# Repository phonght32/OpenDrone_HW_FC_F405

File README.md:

# OpenDrone_FC_F405_HW

Version 3.0

### Overview

OpenDrone Project - Fly Controller hardware using STM32F405RG.

### Specifications

### Layout/Pin map

### Design

#### Schematic

#### PCB

F.Cu

B.Cu

#### 3D top

#### 3D bottom

#### Dimension

### Bill of materials (BOM)

[Download v1.0](Assets/BOM/BOM_OpenDrone_FC_F405_HW_v1.0.xlsx)

[Download v2.0](Assets/BOM/BOM_OpenDrone_FC_F405_HW_v2.0.xlsx)

[Download v3.0](Assets/BOM/BOM_OpenDrone_FC_F405_HW_v3.0.xlsx)

### Gerber

[Download v1.0](Assets/Gerber/Gerber_OpenDrone_FC_F405_HW_v1.0.zip)

[Download v2.0](Assets/Gerber/Gerber_OpenDrone_FC_F405_HW_v2.0.zip)

[Download v3.0](Assets/Gerber/Gerber_OpenDrone_FC_F405_HW_v3.0.zip)

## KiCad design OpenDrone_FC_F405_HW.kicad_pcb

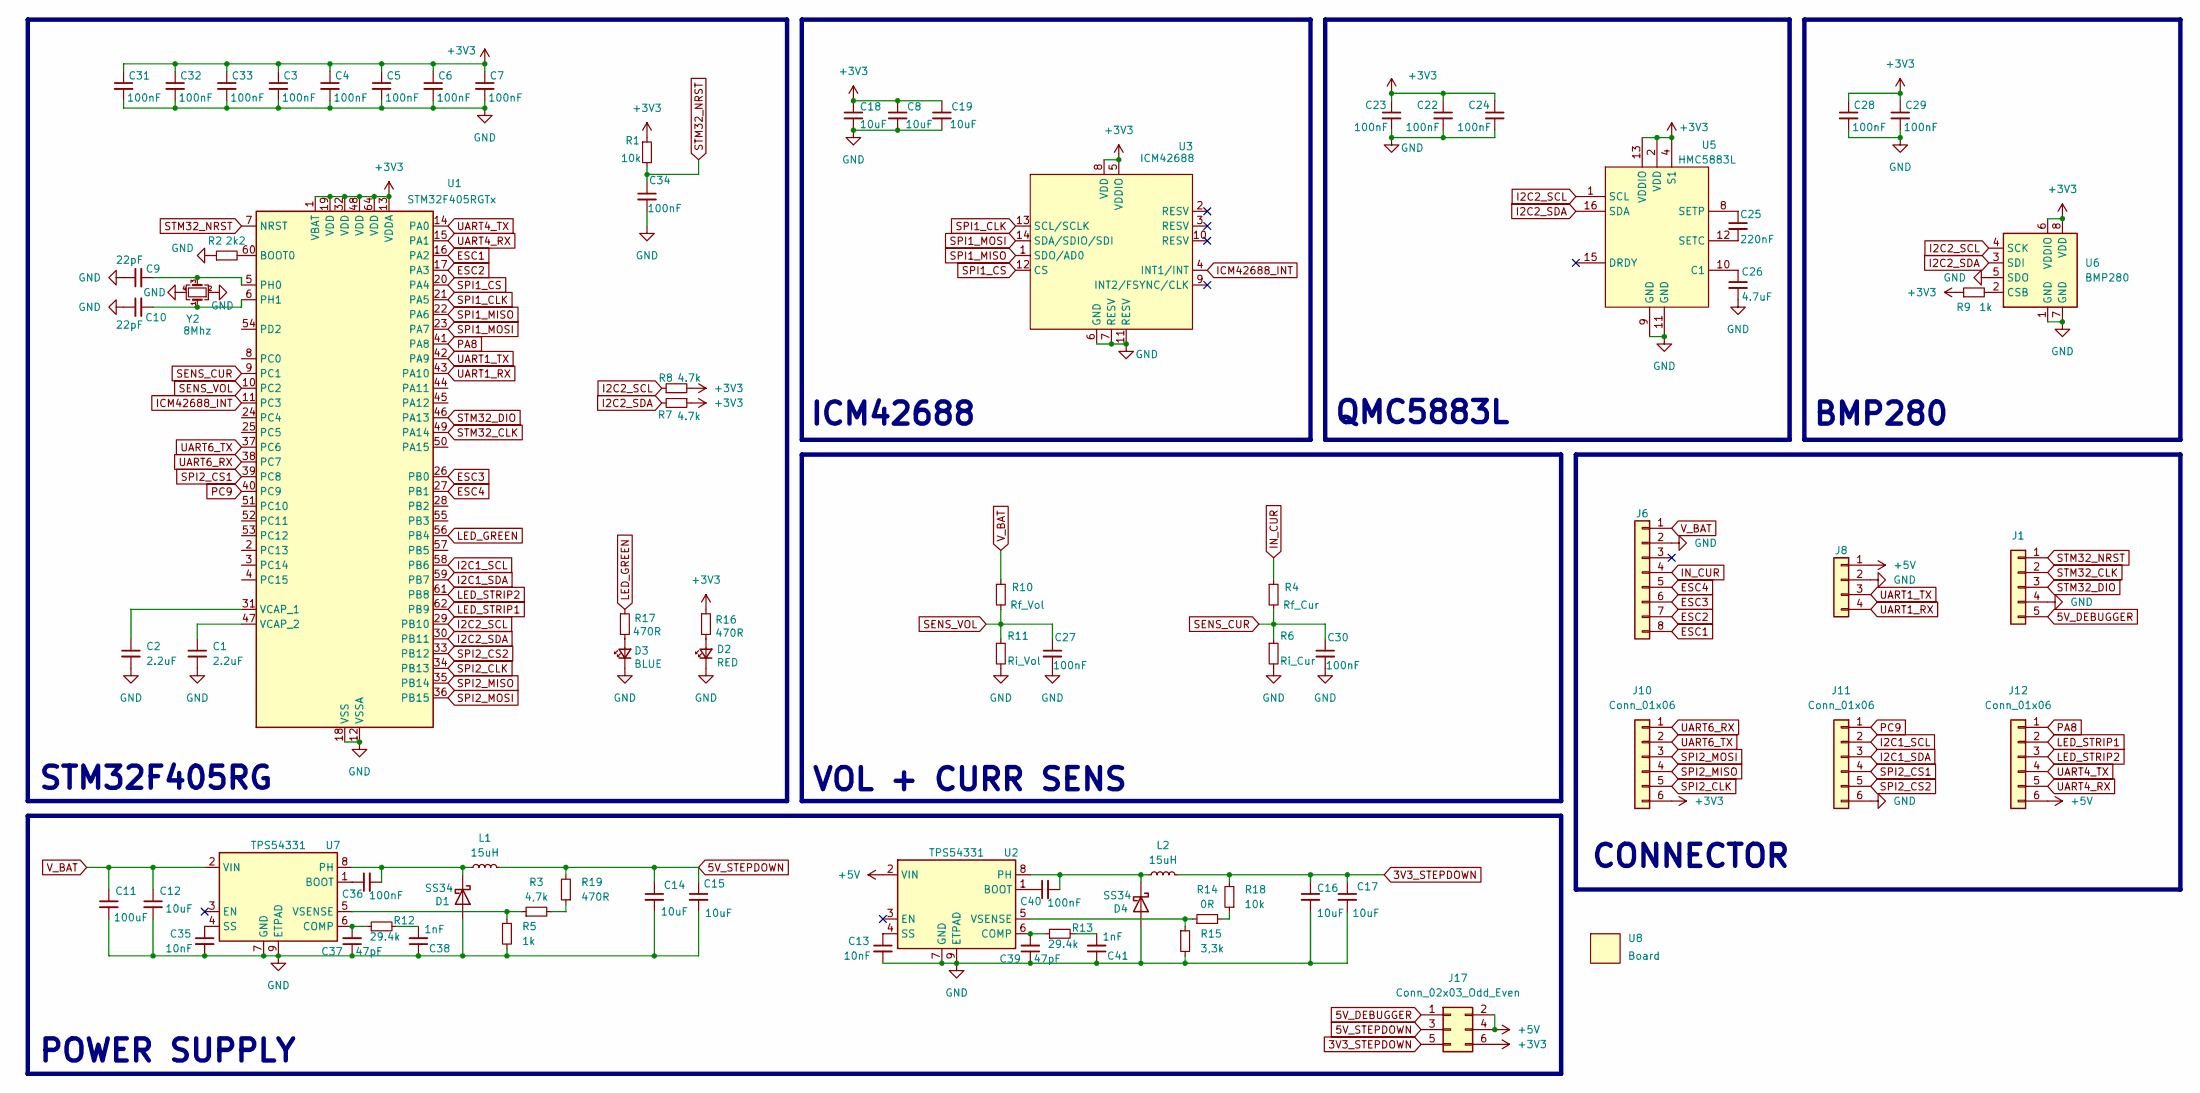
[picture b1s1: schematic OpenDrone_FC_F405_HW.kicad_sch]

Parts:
C1, C2: 2.2uF; C_0402_1005Metric
C3, C4, C5, C6, C7, C22, C23, C24, C27, C28, C29, C30, C31, C32, C33, C34, C36, C40: 100nF; C_0402_1005Metric
C8, C18, C19: 10uF; C_0402_1005Metric
C9, C10: 22pF; C_0402_1005Metric
C11: 100uF; C_1210_3225Metric
C12, C14, C15, C16, C17: 10uF; C_1210_3225Metric
C13, C35: 10nF; C_0402_1005Metric
C25: 220nF; C_0402_1005Metric
C26: 4.7uF; C_0402_1005Metric
C37, C39: 47pF; C_0402_1005Metric
C38, C41: 1nF; C_0402_1005Metric
D1, D4: SS34; D_SMA
D2: RED; LED_0402_1005Metric
D3: BLUE; LED_0402_1005Metric
J1: Conn_01x05; Connector_XH_1x05_P1.25mm_Horizontal
J6: Conn_01x08; Connector_XH_1x08_P1.25mm_Horizontal
J8: Conn_01x04; Connector_XH_1x04_P1.25mm_Horizontal
J10, J11, J12: Conn_01x06; Header_1x06_P2.00mm_Vertical
J17: Conn_02x03_Odd_Even; PinHeader_2x03_P2.00mm_Vertical
L1, L2: 15uH; Inductor_SMD_4D28
R1, R18: 10k; R_0402_1005Metric
R2: 2k2; R_0402_1005Metric
R3: 4,7k; R_0402_1005Metric
R4: Rf_Cur; R_0402_1005Metric
R5, R9: 1k; R_0402_1005Metric
R6: Ri_Cur; R_0402_1005Metric
R7, R8: 4.7k; R_0402_1005Metric
R10: Rf_Vol; R_0402_1005Metric
R11: Ri_Vol; R_0402_1005Metric
R12, R13: 29.4k; R_0402_1005Metric
R14: 0R; R_0402_1005Metric
R15: 3,3k; R_0402_1005Metric
R16, R17, R19: 470R; R_0402_1005Metric
U1: STM32F405RGTx; LQFP-64_10x10mm_P0.5mm
U2, U7: TPS54331; SOIC-8-1EP_3.9x4.9mm_P1.27mm_EP2.29x3mm
U3: ICM42688; LGA-14_3x2.5mm_P0.5mm
U5: HMC5883L; QFN-16_3x3mm_P0.5mm
U6: BMP280; LGA-8_2x2.5mm_P0.65mm
U8: Board; Board_Outline_34x34_Hole_26x26
Y2: 8Mhz; Crystal_SMD_3225-4Pin_3.2x2.5mm

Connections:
3V3_STEPDOWN: C16.1, C17.1, J17.5, L2.2, R18.2
5V_DEBUGGER: J1.5, J17.1
5V_STEPDOWN: C14.1, C15.1, J17.3, L1.2, R19.2
+3V3: C3.1, C4.1, C5.1, C6.1, C7.1, C8.1, C18.1, C19.1, C22.1, C23.1, C24.1, C28.1, C29.1, C31.1, C32.1, C33.1, J10.6, J17.6, R1.1, R7.1, R8.2, R9.1, R16.1, U1.1 (VBAT), U1.13 (VDDA), U1.19 (VDD), U1.32 (VDD), U1.48 (VDD), U1.64 (VDD), U3.5 (VDDIO), U3.8 (VDD), U5.2 (VDD), U5.4 (S1), U5.13 (VDDIO), U6.6 (VDDIO), U6.8 (VDD)
+5V: J8.1, J12.6, J17.2, J17.4, U2.2 (VIN)
ESC1: J6.8, U1.16 (PA2)
ESC2: J6.7, U1.17 (PA3)
ESC3: J6.6, U1.26 (PB0)
ESC4: J6.5, U1.27 (PB1)
GND: C1.2, C2.2, C3.2, C4.2, C5.2, C6.2, C7.2, C8.2, C9.1, C10.1, C11.2, C12.2, C13.2, C14.2, C15.2, C16.2, C17.2, C18.2, C19.2, C22.2, C23.2, C24.2, C26.2, C27.2, C28.2, C29.2, C30.2, C31.2, C32.2, C33.2, C34.2, C35.2, C37.1, C38.1, C39.1, C41.1, D1.2 (A), D2.1 (K), D3.1 (K), D4.2 (A), J1.4, J6.2, J8.2, J11.6, R2.1, R5.2, R6.2, R11.2, R15.2, U1.12 (VSSA), U1.18 (VSS), U1.63 (VSS), U2.7 (GND), U2.9 (ETPAD), U3.6 (GND), U3.7 (RESV), U3.11 (RESV), U5.9 (GND), U5.11 (GND), U6.1 (GND), U6.5 (SDO), U6.7 (GND), U7.7 (GND), U7.9 (ETPAD), Y2.2, Y2.4
I2C1_SCL: J11.2, U1.58 (PB6)
I2C1_SDA: J11.3, U1.59 (PB7)
I2C2_SCL: R8.1, U1.29 (PB10), U5.1 (SCL), U6.4 (SCK)
I2C2_SDA: R7.2, U1.30 (PB11), U5.16 (SDA), U6.3 (SDI)
ICM42688_INT: U1.11 (PC3), U3.4 (INT1/INT)
IN_CUR: J6.4, R4.1
LED_GREEN: R17.1, U1.56 (PB4)
LED_STRIP1: J12.2, U1.62 (PB9)
LED_STRIP2: J12.3, U1.61 (PB8)
unnamed: C38.2, R12.2
unnamed: C41.2, R13.2
unnamed: C36.2, D1.1 (K), L1.1, U7.8 (PH)
unnamed: D2.2 (A), R16.2
unnamed: D3.2 (A), R17.2
unnamed: C40.2, D4.1 (K), L2.1, U2.8 (PH)
unnamed: R14.2, R18.1
unnamed: R3.2, R19.1
unnamed: R2.2, U1.60 (BOOT0)
unnamed: C9.2, U1.5 (PH0), Y2.3
unnamed: C10.2, U1.6 (PH1), Y2.1
unnamed: C2.1, U1.31 (VCAP_1)
unnamed: C1.1, U1.47 (VCAP_2)
unnamed: C40.1, U2.1 (BOOT)
unnamed: C39.2, R13.1, U2.6 (COMP)
unnamed: C13.1, U2.4 (SS)
unnamed: R14.1, R15.1, U2.5 (VSENSE)
unnamed: C26.1, U5.10 (C1)
unnamed: C25.2, U5.12 (SETC)
unnamed: C25.1, U5.8 (SETP)
unnamed: R9.2, U6.2 (CSB)
unnamed: C36.1, U7.1 (BOOT)
unnamed: C37.2, R12.1, U7.6 (COMP)
unnamed: C35.1, U7.4 (SS)
unnamed: R3.1, R5.1, U7.5 (VSENSE)
PA8: J12.1, U1.41 (PA8)
PC9: J11.1, U1.40 (PC9)
SENS_CUR: C30.1, R4.2, R6.1, U1.9 (PC1)
SENS_VOL: C27.1, R10.2, R11.1, U1.10 (PC2)
SPI1_CLK: U1.21 (PA5), U3.13 (SCL/SCLK)
SPI1_CS: U1.20 (PA4), U3.12 (CS)
SPI1_MISO: U1.22 (PA6), U3.1 (SDO/AD0)
SPI1_MOSI: U1.23 (PA7), U3.14 (SDA/SDIO/SDI)
SPI2_CLK: J10.5, U1.34 (PB13)
SPI2_CS1: J11.4, U1.39 (PC8)
SPI2_CS2: J11.5, U1.33 (PB12)
SPI2_MISO: J10.4, U1.35 (PB14)
SPI2_MOSI: J10.3, U1.36 (PB15)
STM32_CLK: J1.2, U1.49 (PA14)
STM32_DIO: J1.3, U1.46 (PA13)
STM32_NRST: C34.1, J1.1, R1.2, U1.7 (NRST)
UART1_RX: J8.4, U1.43 (PA10)
UART1_TX: J8.3, U1.42 (PA9)
UART4_RX: J12.5, U1.15 (PA1)
UART4_TX: J12.4, U1.14 (PA0)
UART6_RX: J10.1, U1.38 (PC7)
UART6_TX: J10.2, U1.37 (PC6)
V_BAT: C11.1, C12.1, J6.1, R10.1, U7.2 (VIN)

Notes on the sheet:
ICM42688
QMC5883L
BMP280
POWER SUPPLY
CONNECTOR
VOL + CURR SENS
STM32F405RG

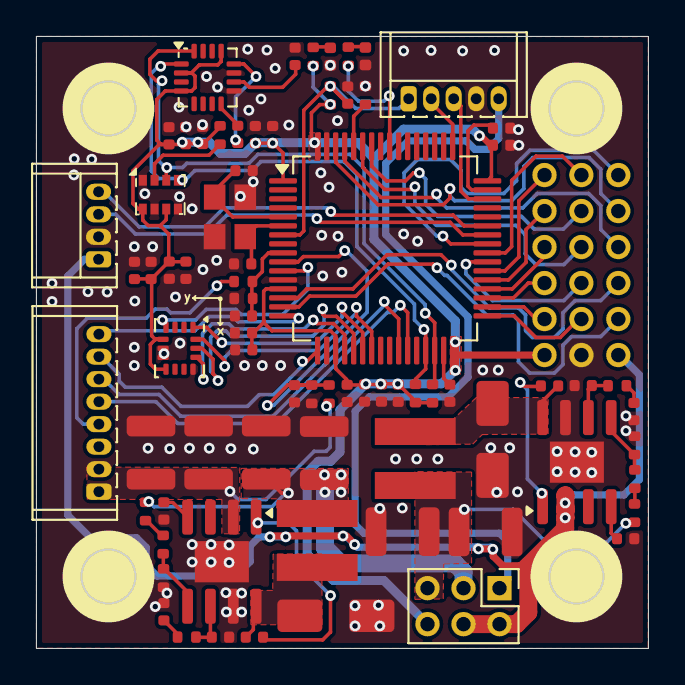
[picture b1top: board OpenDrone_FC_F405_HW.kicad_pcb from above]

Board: 2 copper layers, 33.9 x 34.0 mm, 79 parts (0 on the bottom side), 67 nets.

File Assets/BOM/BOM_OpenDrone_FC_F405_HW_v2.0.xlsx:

Reference | Value | Footprint | Datasheet | Qty | DNP
C1,C2 | 2.2uF | Capacitor_SMD:C_0402_1005Metric | ~ | 2
C3,C4,C5,C6,C7,C20,C22,C23,C24,C27,C28,C29,C30,C31,C32,C33,C34,C36,C40 | 100nF | Capacitor_SMD:C_0402_1005Metric | ~ | 19
C9,C10 | 22pF | Capacitor_SMD:C_0402_1005Metric | ~ | 2
C13,C19,C35 | 10nF | Capacitor_SMD:C_0402_1005Metric | ~ | 3
C18 | 10uF | Capacitor_SMD:C_0402_1005Metric | ~ | 1
C21 | 2.2nF | Capacitor_SMD:C_0402_1005Metric | ~ | 1
C25 | 220nF | Capacitor_SMD:C_0402_1005Metric | ~ | 1
C26 | 4.7uF | Capacitor_SMD:C_0402_1005Metric | ~ | 1
C37,C39 | 47pF | Capacitor_SMD:C_0402_1005Metric | ~ | 2
C38,C41 | 1nF | Capacitor_SMD:C_0402_1005Metric | ~ | 2
C11 | 100uF | Capacitor_SMD:C_1210_3225Metric | ~ | 1
C12,C14,C15,C16,C17 | 10uF | Capacitor_SMD:C_1210_3225Metric | ~ | 5
J17 | Conn_02x03_Odd_Even | Connector_PinHeader_2.00mm:PinHeader_2x03_P2.00mm_Vertical | ~ | 1
Y2 | 8Mhz | Crystal:Crystal_SMD_3225-4Pin_3.2x2.5mm | ~ | 1
D1,D4 | SS34 | Diode_SMD:D_SMA | ~ | 2
U8 | Board | Footprint:Board_Outline_34x34_Hole_26x26 |  | 1
J8 | Conn_01x04 | Footprint:Connector_XH_1x04_P1.25mm_Horizontal | ~ | 1
J1 | Conn_01x05 | Footprint:Connector_XH_1x05_P1.25mm_Horizontal | ~ | 1
J6 | Conn_01x08 | Footprint:Connector_XH_1x08_P1.25mm_Horizontal | ~ | 1
J11,J12,J16 | Conn_01x05 | Footprint:Header_1x05_P2.00mm_Vertical | ~ | 3
J2,J3,J4,J5,J7,J9,J13,J14 | Conn_01x02 | Footprint:HolePad_1x2 | ~ | 8
L1,L2 | 15uH | Footprint:Inductor_SMD_4D28 | ~ | 2
U6 | BMP280 | Footprint:LGA-8_2x2.5mm_P0.65mm | https://ae-bst.resource.bosch.com/media/_tech/media/datashee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 | 1
U5 | HMC5883L | Footprint:QFN-16_3x3mm_P0.5mm |  | 1
U4 | MPU6000 | Footprint:QFN-24-1EP_4x4mm_P0.5mm_EP2.15x2.15mm |  | 1
D2 | RED | LED_SMD:LED_0402_1005Metric | ~ | 1
D3 | BLUE | LED_SMD:LED_0402_1005Metric | ~ | 1
D6 | GREEN | LED_SMD:LED_0402_1005Metric | ~ | 1
U1 | STM32F405RGTx | Package_QFP:LQFP-64_10x10mm_P0.5mm | https://www.st.com/resource/en/datasheet/stm32f405rg.pdf | 1
U2,U7 | TPS54331 | Package_SO:SOIC-8-1EP_3.9x4.9mm_P1.27mm_EP2.29x3mm |  | 2
R1,R18 | 10k | Resistor_SMD:R_0402_1005Metric | ~ | 2
R2 | 2k2 | Resistor_SMD:R_0402_1005Metric | ~ | 1
R3 | 4,7k | Resistor_SMD:R_0402_1005Metric | ~ | 1
R4 | Rf_Cur | Resistor_SMD:R_0402_1005Metric | ~ | 1
R5,R9 | 1k | Resistor_SMD:R_0402_1005Metric | ~ | 2
R6 | Ri_Cur | Resistor_SMD:R_0402_1005Metric | ~ | 1
R7,R8 | 4.7k | Resistor_SMD:R_0402_1005Metric | ~ | 2
R10 | Rf_Vol | Resistor_SMD:R_0402_1005Metric | ~ | 1
R11 | Ri_Vol | Resistor_SMD:R_0402_1005Metric | ~ | 1
R12,R13 | 29.4k | Resistor_SMD:R_0402_1005Metric | ~ | 2
R14 | 0R | Resistor_SMD:R_0402_1005Metric | ~ | 1
R15 | 3,3k | Resistor_SMD:R_0402_1005Metric | ~ | 1
R16,R17,R19,R25 | 470R | Resistor_SMD:R_0402_1005Metric | ~ | 4

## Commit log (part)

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2024-04-13 Initial project
2024-04-13 update LICENSE
2024-04-14 add LoRa IRQ
2024-04-21 use mpu6050 and change spi pinout
2024-06-08 update 3d
2024-06-08 update pcb
2024-06-08 update gerber
2024-07-02 update project
2024-07-03 update placement
2024-07-10 update demo
2024-07-10 update BOM
2024-07-10 update schematic
2024-09-03 complete schematic & PCB v2.0
2024-09-03 complete v2.0
2024-09-03 remove gerber folder
2024-11-28 add README v2.0
2024-11-28 add README
2024-12-03 add header 1x06
2024-12-03 add ICM42688
2024-12-05 update routing
2024-12-06 add footprint
2024-12-06 add KiCad-Lib
2024-12-06 update submodule
2024-12-06 update library
2024-12-06 update setting
2024-12-23 add BOM
2024-12-23 add gerber
2024-12-23 add schematic
2024-12-23 add image demo
